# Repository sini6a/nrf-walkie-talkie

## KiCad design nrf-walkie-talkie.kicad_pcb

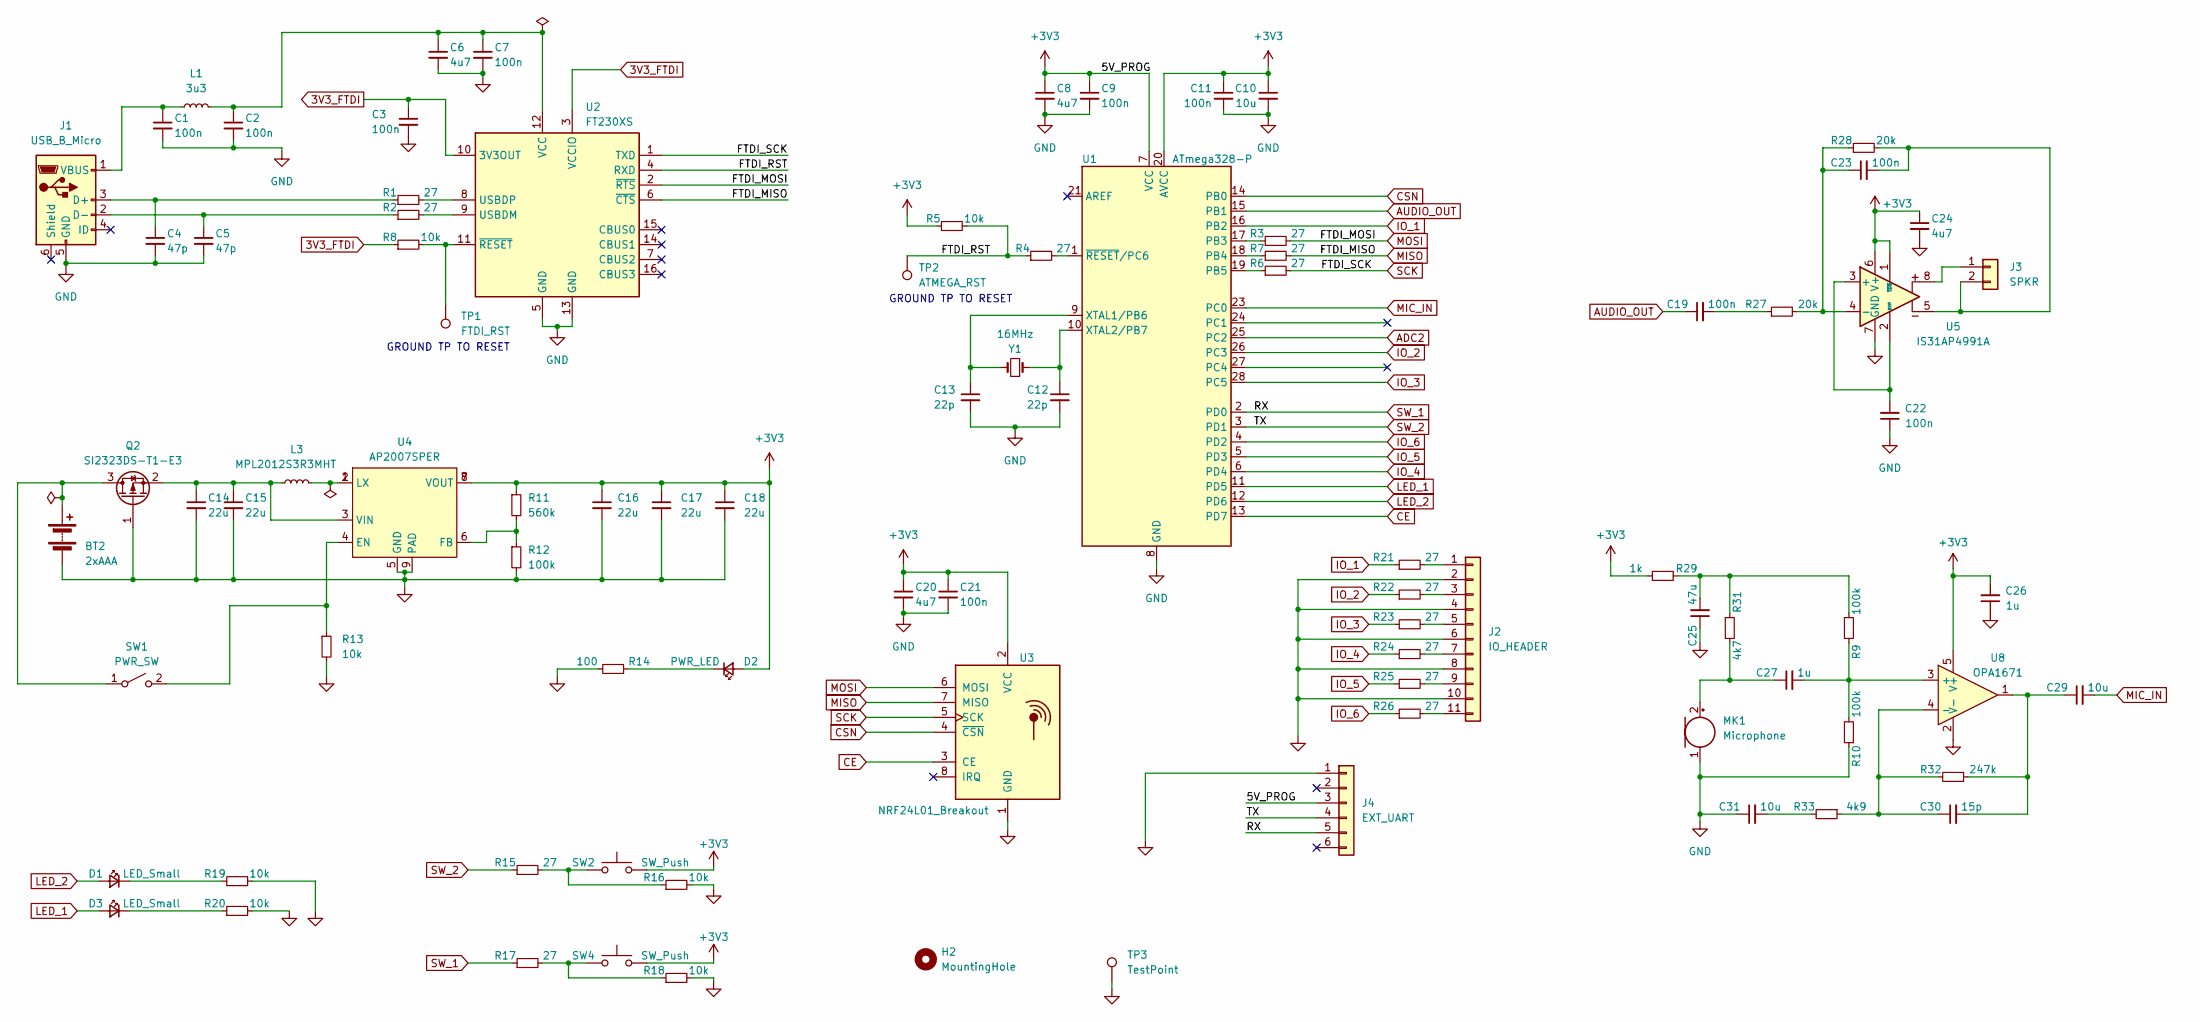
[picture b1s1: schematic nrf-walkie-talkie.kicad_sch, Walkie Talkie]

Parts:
BT2: 2xAAA; BH-AAA-B5AK001; LCSC C964882
C1, C2, C3, C7, C9, C11, C19, C21, C22, C23: 100n; C_0603_1608Metric
C4, C5: 47p; C_0603_1608Metric
C6, C8, C20, C24: 4u7; C_0805_2012Metric
C10, C29, C31: 10u; C_0805_2012Metric
C12, C13: 22p; C_0603_1608Metric
C14, C15, C16, C17: 22u; C_0805_2012Metric; LCSC C45783
C18: 22u; C_0805_2012Metric
C25: 47u; C_0805_2012Metric
C26, C27: 1u; C_0805_2012Metric
C30: 15p; C_0603_1608Metric
D1, D3: LED_Small; LED_0805_2012Metric
D2: PWR_LED; LED_0805_2012Metric; LCSC C84256
H2: MountingHole; MountingHole_2.2mm_M2_DIN965
J1: USB_B_Micro; USB_Micro-B_Amphenol_10118194_Horizontal
J2: IO_HEADER; PinSocket_1x11_P1.27mm_Vertical
J3: SPKR; PinSocket_1x02_P2.54mm_Vertical
J4: EXT_UART; PinHeader_1x06_P2.54mm_Vertical
L1: 3u3; L_0805_2012Metric
L3: MPL2012S3R3MHT; L_0805_2012Metric
MK1: Microphone; CMEJ-0627-42-P
Q2: SI2323DS-T1-E3; SOT-23; LCSC C141511
R1, R2, R3, R4, R6, R7, R15, R17, R21, R22, R23, R24, R25, R26: 27; R_0603_1608Metric
R5, R8, R16, R18, R19, R20: 10k; R_0603_1608Metric
R9, R10: 100k; R_0603_1608Metric
R11: 560k; R_0603_1608Metric; LCSC C25602
R12: 100k; R_0603_1608Metric; LCSC C25803
R13: 10k; R_0603_1608Metric; LCSC C25804
R14: 100; R_0603_1608Metric; LCSC C22775
R27, R28: 20k; R_0603_1608Metric
R29: 1k; R_0603_1608Metric
R31: 4k7; R_0603_1608Metric
R32: 247k; R_0603_1608Metric
R33: 4k9; R_0603_1608Metric
SW1: PWR_SW; MS1206; LCSC C2681575
SW2, SW4: SW_Push; SW_Tactile_SPST_Angled_PTS645Vx58-2LFS
TP1: FTDI_RST; TestPoint_Pad_1.0x1.0mm
TP2: ATMEGA_RST; TestPoint_Pad_1.0x1.0mm
TP3: TestPoint; TestPoint_Pad_1.0x1.0mm
U1: ATmega328-P; DIP-28_W7.62mm
U2: FT230XS; SSOP-16_3.9x4.9mm_P0.635mm
U3: NRF24L01_Breakout; nRF24L01_Breakout
U4: AP2007SPER; SOIC-8-1EP_3.9x4.9mm_P1.27mm_EP2.41x3.3mm; LCSC C130338
U5: IS31AP4991A; SOP-8_3.9x4.9mm_P1.27mm
U8: OPA1671; SOT-23-5
Y1: 16MHz; Crystal_SMD_HC49-SD

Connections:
3V3_FTDI: C3.1, R8.1, U2.3 (VCCIO), U2.10 (3V3OUT)
+3V3: C8.1, C9.1, C10.1, C11.1, C16.1, C17.1, C18.1, C20.1, C21.1, C24.1, C26.2, D2.2 (A), J4.3, R5.1, R11.1, R29.1, SW2.2, SW4.2, U1.7 (VCC), U1.20 (AVCC), U3.2 (VCC), U4.7 (VOUT), U4.8 (VOUT), U5.1 (~SDB), U5.6 (V+), U8.5 (V+)
/FTDI_RST: R4.1, R5.2, TP2.1, U2.4 (RXD)
ADC2: U1.25 (PC2)
AUDIO_OUT: C19.1, U1.15 (PB1)
CE: U1.13 (PD7), U3.3 (CE)
CSN: U1.14 (PB0), U3.4 (~CSN)
GND: BT2.2 (-), C1.2, C2.2, C3.2, C4.2, C5.2, C6.2, C7.2, C8.2, C9.2, C10.2, C11.2, C12.2, C13.2, C14.2, C15.2, C16.2, C17.2, C18.2, C20.2, C21.2, C22.1, C24.2, C25.1, C26.1, C31.1, J1.5 (GND), J2.2, J2.4, J2.6, J2.8, J2.10, J4.1, MK1.1 (-), Q2.1 (G), R10.1, R12.2, R13.2, R14.2, R16.2, R18.2, R19.2, R20.2, TP3.1, U1.8 (GND), U1.22 (GND), U2.5 (GND), U2.13 (GND), U3.1 (GND), U4.5 (GND), U4.9 (PAD), U5.7 (GND), U8.2 (V-)
IO_1: R21.1, U1.16 (PB2)
IO_2: R22.1, U1.26 (PC3)
IO_3: R23.1, U1.28 (PC5)
IO_4: R24.1, U1.6 (PD4)
IO_5: R25.1, U1.5 (PD3)
IO_6: R26.1, U1.4 (PD2)
LED_1: D3.2 (A), U1.11 (PD5)
LED_2: D1.2 (A), U1.12 (PD6)
MIC_IN: C29.2, U1.23 (PC0)
MISO: R7.2, U2.6 (~CTS), U3.7 (MISO)
MOSI: R3.2, U2.2 (~RTS), U3.6 (MOSI)
unnamed: BT2.1 (+), Q2.3 (D), SW1.1 (A)
unnamed: C19.2, R27.1
unnamed: C25.2, R9.1, R29.2, R31.1
unnamed: C29.1, C30.2, R32.1, U8.1
unnamed: C31.2, R33.2
unnamed: D1.1 (K), R19.1
unnamed: D2.1 (K), R14.1
unnamed: D3.1 (K), R20.1
unnamed: C4.1, J1.3 (D+), R1.1
unnamed: C5.1, J1.2 (D-), R2.1
unnamed: C1.1, J1.1 (VBUS), L1.1
unnamed: J2.1, R21.2
unnamed: J2.3, R22.2
unnamed: J2.5, R23.2
unnamed: J2.7, R24.2
unnamed: J2.9, R25.2
unnamed: J2.11, R26.2
unnamed: J3.1, U5.8
unnamed: C23.2, J3.2, R28.2, U5.5
unnamed: L3.2, U4.1 (LX), U4.2 (LX)
unnamed: C27.1, MK1.2 (+), R31.2
unnamed: C14.1, C15.1, L3.1, Q2.2 (S), U4.3 (VIN)
unnamed: R15.2, R16.1, SW2.1
unnamed: R17.2, R18.1, SW4.1
unnamed: R13.1, SW1.2 (B), U4.4 (EN)
unnamed: R3.1, U1.17 (PB3)
unnamed: R7.1, U1.18 (PB4)
unnamed: R6.1, U1.19 (PB5)
unnamed: C13.1, U1.9 (XTAL1/PB6), Y1.2
unnamed: C12.1, U1.10 (XTAL2/PB7), Y1.1
unnamed: R4.2, U1.1 (~RESET/PC6)
unnamed: R2.2, U2.9 (USBDM)
unnamed: R1.2, U2.8 (USBDP)
unnamed: C2.1, C6.1, C7.1, L1.2, U2.12 (VCC)
unnamed: R8.2, TP1.1, U2.11 (~RESET)
unnamed: R11.2, R12.1, U4.6 (FB)
unnamed: C22.2, U5.2 (BYP), U5.3 (+)
unnamed: C23.1, R27.2, R28.1, U5.4 (-)
unnamed: C27.2, R9.2, R10.2, U8.3 (+)
unnamed: C30.1, R32.2, R33.1, U8.4 (-)
SCK: R6.2, U2.1 (TXD), U3.5 (SCK)
SW_1: J4.5, R17.1, U1.2 (PD0)
SW_2: J4.4, R15.1, U1.3 (PD1)

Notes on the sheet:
GROUND TP TO RESET

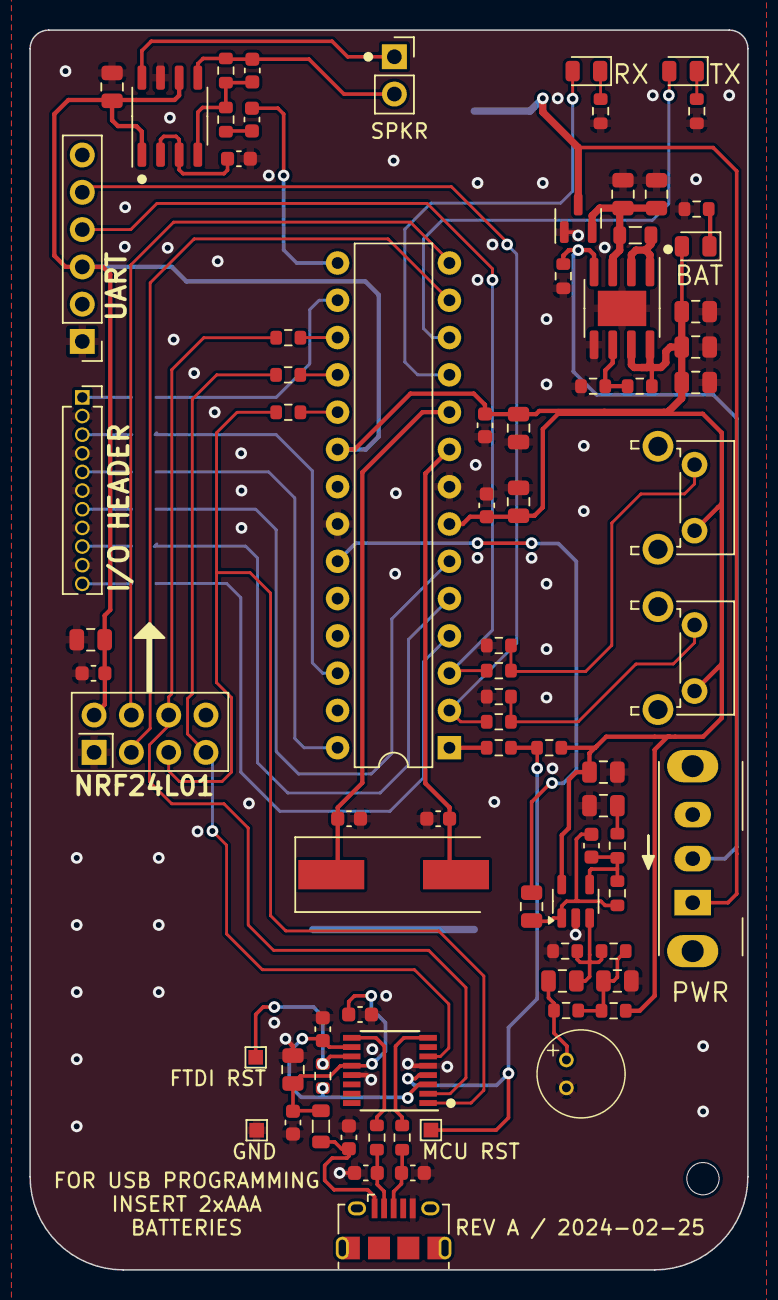
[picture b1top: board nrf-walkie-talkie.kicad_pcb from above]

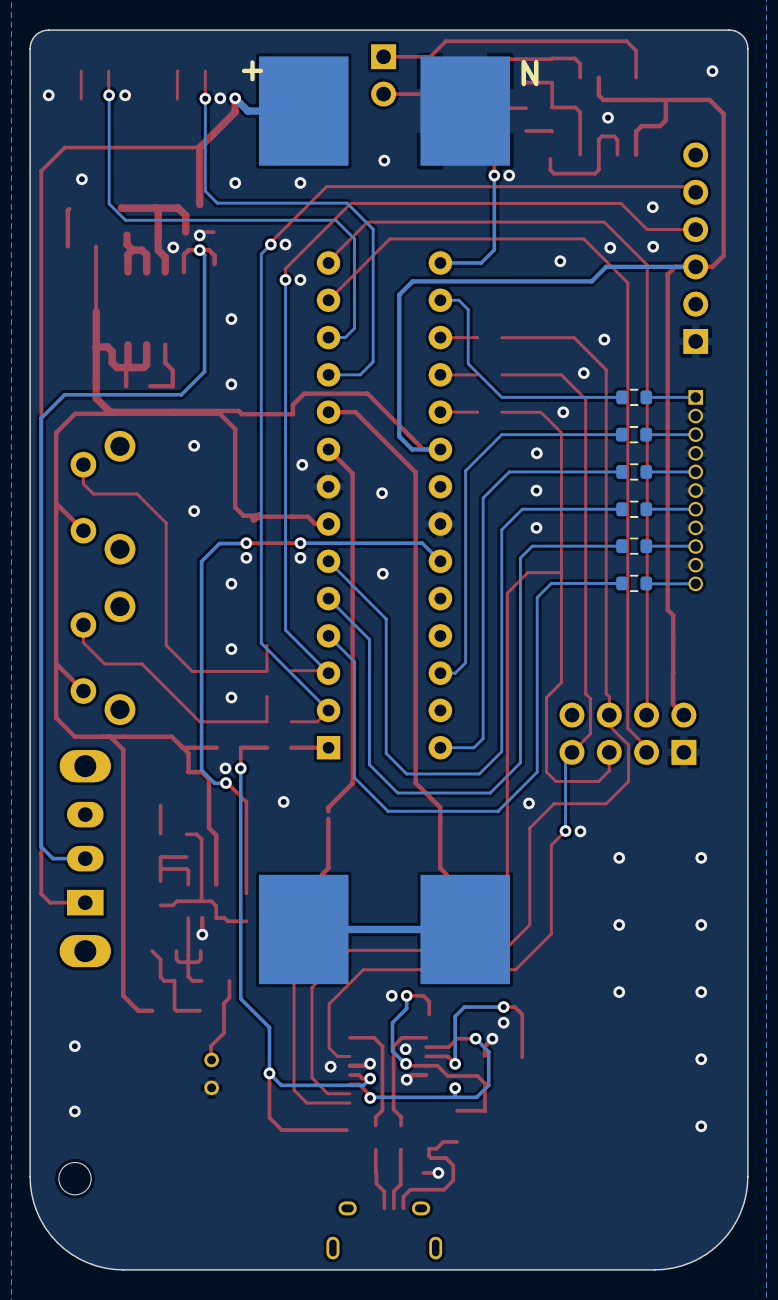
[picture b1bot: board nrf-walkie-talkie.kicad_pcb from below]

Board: 2 copper layers, 48.9 x 84.5 mm, 88 parts (7 on the bottom side), 61 nets.

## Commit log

2024-09-24 initial design
